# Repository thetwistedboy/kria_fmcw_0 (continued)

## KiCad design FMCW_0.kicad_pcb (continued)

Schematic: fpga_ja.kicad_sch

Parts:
C26: 2.2u; C_0402_1005Metric; Digikey PN 1276-1108-1-ND
C30, C32: 100n; C_0402_1005Metric; Digikey PN 1276-1043-1-ND
D4: GREEN; LED_0603_1608Metric; Digikey PN 160-1446-1-ND
J1: Conn_02x07_Odd_Even; PinHeader_2x07_P2.00mm_Horizontal; Digikey PN WM9841-ND
LCD1: MSP3520; ILI9488_SPI_TFT
R39, R40, R41, R42, R44, R45, R46, R47, R48, R49, R50: 22; R_0402_1005Metric; Digikey PN 541-22.0LCT-ND
R43, R101, R102: 0; R_0402_1005Metric; Digikey PN 311-0.0JRCT-ND
R95: 470; R_0402_1005Metric; Digikey PN 311-470LRCT-ND
R99, R100: 4.7k; R_0402_1005Metric; Digikey PN 311-4.7KJRCT-ND
R103: DNI; R_0402_1005Metric
SW2: SW_Push; SW_Push_1P1T_NO_CK_KMR2; Digikey PN 108-KMR211GLFSCT-ND
SW3: SW_DIP_x04; SW_DIP_SPSTx04_Slide_Omron_A6H-4101_W6.15mm_P1.27mm; Digikey PN 39-A6H-4101-ND
TP1, TP2, TP3: TestPoint; TestPoint_Keystone_5015_Micro_Mini
U16: Kria K24 SoM; Kria_K24
U31: MCP3221; SOT-23-5; Digikey PN MCP3221A5T-E/OTCT-ND

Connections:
+1V8: J1.2, U16.JA_D1 (VCCO_HPA), U16.JA_D2 (VCCO_HPA); also elsewhere on the board
+3V3: C26.1, C30.2, C32.2, LCD1.1 (VCC), R99.2, R100.2, U16.JA_B13 (VCCO_HDA), U16.JA_B14 (VCCO_HDA), U31.1 (V_{DD}); also elsewhere on the board
+5V0: U16.JA_A59 (VCC_SOM), U16.JA_A60 (VCC_SOM), U16.JA_B60 (VCC_SOM), U16.JA_C59 (VCC_SOM), U16.JA_C60 (VCC_SOM), U16.JA_D60 (VCC_SOM); also elsewhere on the board
/RFFE/rf_ps_pg: U16.JA_C15 (PS_POR_B); also elsewhere on the board
/RFFE/rffe_ps_en: R101.2, R103.1; also elsewhere on the board
/RFFE/sample_clk: U16.JA_D16 (HDA_00_CC); also elsewhere on the board
/RFFE/src_ce: U16.JA_A4 (HPA_06N); also elsewhere on the board
/RFFE/src_clk: U16.JA_A6 (HPA_CLK0P_CLK); also elsewhere on the board
/RFFE/src_data: U16.JA_B1 (HPA_05P_CC); also elsewhere on the board
/RFFE/src_le: U16.JA_A3 (HPA_06P); also elsewhere on the board
/RFFE/src_mod: U16.JA_A7 (HPA_CLK0N); also elsewhere on the board
/RFFE/src_muxout: U16.JA_B2 (HPA_05N_CC); also elsewhere on the board
/RFFE/src_trig1: U16.JA_D4 (HPA_02P); also elsewhere on the board
/RFFE/src_trig2: U16.JA_D5 (HPA_02N); also elsewhere on the board
/efuse/Imon: U31.3 (A_{IN}); also elsewhere on the board
/fpga/5V0_PG: U16.JA_B26 (PWROFF_C2M_B); also elsewhere on the board
/fpga/eth/eth_rx_clk: U16.JA_D32 (MIO44); also elsewhere on the board
/fpga/eth/eth_rx_ctrl: U16.JA_C36 (MIO49); also elsewhere on the board
/fpga/eth/eth_rx_d0: U16.JA_D33 (MIO45); also elsewhere on the board
/fpga/eth/eth_rx_d1: U16.JA_D34 (MIO46); also elsewhere on the board
/fpga/eth/eth_rx_d2: U16.JA_C34 (MIO47); also elsewhere on the board
/fpga/eth/eth_rx_d3: U16.JA_C35 (MIO48); also elsewhere on the board
/fpga/eth/eth_tx_clk: U16.JA_B32 (MIO38); also elsewhere on the board
/fpga/eth/eth_tx_ctrl: U16.JA_A36 (MIO43); also elsewhere on the board
/fpga/eth/eth_tx_d0: U16.JA_B33 (MIO39); also elsewhere on the board
/fpga/eth/eth_tx_d1: U16.JA_B34 (MIO40); also elsewhere on the board
/fpga/eth/eth_tx_d2: U16.JA_A34 (MIO41); also elsewhere on the board
/fpga/eth/eth_tx_d3: U16.JA_A35 (MIO42); also elsewhere on the board
/fpga/eth/md_mdc: U16.JA_D13 (HPA_14P); also elsewhere on the board
/fpga/eth/md_mdio: U16.JA_D14 (HPA_14N); also elsewhere on the board
/fpga/fpga_ja/PS_SRST_N: J1.14, SW2.2, U16.JA_C16 (PS_SRST_C2M_B)
/fpga/fpga_ja/PS_SUPPLY_START: R102.2, R103.2
/fpga/fpga_ja/TCK: R41.2, U16.JA_A25 (JTAG_TCK_C2M)
/fpga/fpga_ja/TDI: R39.2, U16.JA_A24 (JTAG_TDI_C2M)
/fpga/fpga_ja/TDO: R40.2, U16.JA_A23 (JTAG_TDO_M2C)
/fpga/fpga_ja/TMS: R42.2, U16.JA_A22 (JTAG_TMS_C2M)
/fpga/fpga_ja/i2c_33_scl: R99.1, U16.JA_C22 (HDA_18), U31.5 (SCL)
/fpga/fpga_ja/i2c_33_sda: R100.1, U16.JA_C23 (HDA_19), U31.4 (SDA)
/fpga/fpga_ja/tft_cs_n: R44.1, U16.JA_D22 (HDA_14)
/fpga/fpga_ja/tft_dc: R46.1, U16.JA_D20 (HDA_12)
/fpga/fpga_ja/tft_led: R49.1, U16.JA_C19 (HDA_07)
/fpga/fpga_ja/tft_miso: R50.1, U16.JA_C18 (HDA_06)
/fpga/fpga_ja/tft_mosi: R47.1, U16.JA_D18 (HDA_02)
/fpga/fpga_ja/tft_rst: R45.1, U16.JA_D21 (HDA_13)
/fpga/fpga_ja/tft_sck: R48.1, U16.JA_D17 (HDA_01)
/fpga/fpga_ja/uart_rxd: U16.JA_A43 (MIO74); also elsewhere on the board
/fpga/fpga_ja/uart_txd: U16.JA_A44 (MIO75); also elsewhere on the board
/fpga/fpga_ja/ulpi_clkout: U16.JA_D36 (MIO52); also elsewhere on the board
/fpga/fpga_ja/ulpi_d0: U16.JA_C39 (MIO56); also elsewhere on the board
/fpga/fpga_ja/ulpi_d1: U16.JA_C40 (MIO57); also elsewhere on the board
/fpga/fpga_ja/ulpi_d2: U16.JA_D38 (MIO54); also elsewhere on the board
/fpga/fpga_ja/ulpi_d3: U16.JA_B41 (MIO59); also elsewhere on the board
/fpga/fpga_ja/ulpi_d4: U16.JA_B42 (MIO60); also elsewhere on the board
/fpga/fpga_ja/ulpi_d5: U16.JA_A38 (MIO61); also elsewhere on the board
/fpga/fpga_ja/ulpi_d6: U16.JA_A39 (MIO62); also elsewhere on the board
/fpga/fpga_ja/ulpi_d7: U16.JA_A40 (MIO63); also elsewhere on the board
/fpga/fpga_ja/ulpi_dir: U16.JA_D37 (MIO53); also elsewhere on the board
/fpga/fpga_ja/ulpi_nxt: U16.JA_C38 (MIO55); also elsewhere on the board
/fpga/fpga_ja/ulpi_stp: U16.JA_B40 (MIO58); also elsewhere on the board
/fpga/fpga_ja/usb_reset: U16.JA_D40 (MIO64); also elsewhere on the board
GND: C26.2, C30.1, C32.1, D4.1 (K), J1.1, J1.3, J1.5, J1.7, J1.9, J1.11, J1.13, LCD1.2 (GND), R43.1, SW2.1, SW3.5, SW3.6, SW3.7, SW3.8, U16.JA_A2 (GND), U16.JA_A5 (GND), U16.JA_A8 (GND), U16.JA_A11 (GND), U16.JA_A14 (GND), U16.JA_A18 (GND), U16.JA_A21 (GND), U16.JA_A26 (GND), U16.JA_A33 (GND), U16.JA_A37 (GND), U16.JA_A41 (GND), U16.JA_A45 (GND), U16.JA_A46 (GND), U16.JA_A49 (GND), U16.JA_A50 (GND), U16.JA_A53 (GND), U16.JA_A54 (GND), U16.JA_A57 (GND), U16.JA_A58 (GND), U16.JA_B3 (GND), U16.JA_B6 (GND), U16.JA_B9 (GND), U16.JA_B12 (GND), U16.JA_B15 (GND), U16.JA_B19 (GND), U16.JA_B23 (GND), U16.JA_B27 (GND), U16.JA_B31 (GND), U16.JA_B35 (GND), U16.JA_B39 (GND), U16.JA_B43 (GND), U16.JA_B47 (GND), U16.JA_B48 (GND), U16.JA_B51 (GND), U16.JA_B52 (GND), U16.JA_B55 (GND), U16.JA_B56 (GND), U16.JA_B59 (GND), U16.JA_C1 (GND), U16.JA_C2 (GND), U16.JA_C5 (GND), U16.JA_C8 (GND), U16.JA_C11 (GND), U16.JA_C14 (GND), U16.JA_C17 (GND), U16.JA_C21 (GND), U16.JA_C25 (GND), U16.JA_C29 (GND), U16.JA_C33 (GND), U16.JA_C37 (GND), U16.JA_C41 (GND), U16.JA_C46 (GND), U16.JA_C49 (GND), U16.JA_C50 (GND), U16.JA_C53 (GND), U16.JA_C54 (GND), U16.JA_C57 (GND), U16.JA_C58 (GND), U16.JA_D3 (GND), U16.JA_D6 (GND), U16.JA_D9 (GND), U16.JA_D12 (GND), U16.JA_D15 (GND), U16.JA_D19 (GND), U16.JA_D23 (GND), U16.JA_D27 (GND), U16.JA_D31 (GND), U16.JA_D35 (GND), U16.JA_D39 (GND), U16.JA_D43 (GND), U16.JA_D47 (GND), U16.JA_D48 (GND), U16.JA_D51 (GND), U16.JA_D52 (GND), U16.JA_D55 (GND), U16.JA_D56 (GND), U16.JA_D59 (GND), U31.2 (V_{SS}); also elsewhere on the board
unnamed: D4.2 (A), R95.1
unnamed: J1.4, R42.1
unnamed: J1.6, R41.1
unnamed: J1.8, R40.1
unnamed: J1.10, R39.1
unnamed: LCD1.3 (CS), R44.2
unnamed: LCD1.5 (DC), R46.2
unnamed: LCD1.8 (LED), R49.2
unnamed: LCD1.4 (RST), R45.2
unnamed: LCD1.7 (SCK), R48.2
unnamed: LCD1.6 (SDI), R47.2
unnamed: LCD1.9 (SDO), R50.2
unnamed: R95.2, U16.JA_B16 (HDA_03)
unnamed: TP3.1 (1_1), U16.JA_A15 (HDA_09)
unnamed: TP1.1 (1_1), U16.JA_A16 (HDA_10)
unnamed: TP2.1 (1_1), U16.JA_A17 (HDA_11)
unnamed: SW3.1, U16.JA_A27 (MODE0_C2M)
unnamed: SW3.2, U16.JA_A28 (MODE1_C2M)
unnamed: SW3.3, U16.JA_A29 (MODE2_C2M)
unnamed: SW3.4, U16.JA_A30 (MODE3_C2M)
unnamed: R101.1, U16.JA_A20 (VCCOEN_PL_M2C)
unnamed: R102.1, U16.JA_A19 (VCCOEN_PS_M2C)
unnamed: R43.2, U16.JA_A1 (VCC_BATT)

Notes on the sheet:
HPIO
MDIO MIO50-51
USB0 MIO52-63
GEM1 MIO38-49

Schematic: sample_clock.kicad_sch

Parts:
C1, C2: 100n; C_0402_1005Metric; Digikey PN 1276-1043-1-ND
FB1: FerriteBead_Small; R_0402_1005Metric; Digikey PN 490-5203-1-ND
R1, R3, R4: 10k; R_0402_1005Metric; Digikey PN RMCF0402FT10K0CT-ND
R2, R6, R7: 22; R_0402_1005Metric; Digikey PN 541-22.0LCT-ND
R5, R8: 49.9; R_0402_1005Metric; Digikey PN P49.9LCT-ND
U3: LMK1C1103A; TSSOP-8_4.4x3mm_P0.65mm; Digikey PN 296-LMK1C1103APWRCT-ND
Y1: ECS-2520MV-160-BN; Oscillator_SMD_ECS_2520MV-xxx-xx-4Pin_2.5x2.0mm; Digikey PN 50-ECS-2520MV-160-BN-TRCT-ND

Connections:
+3V3: C2.1, FB1.1, R4.1, U3.6 (VDD); also elsewhere on the board
/RFFE/ADC/sample_clk: R8.2; also elsewhere on the board
/RFFE/sample_clk: R6.2; also elsewhere on the board
/RFFE/sample_clk_out: R7.2; also elsewhere on the board
/RFFE/sample_clock/clk0: R5.2; also elsewhere on the board
GND: C1.2, C2.2, R3.2, U3.4 (GND), Y1.2 (GND); also elsewhere on the board
unnamed: R4.2, U3.2 (1G)
unnamed: R2.2, R3.1, U3.1 (CLKIN)
unnamed: R5.1, U3.3 (Y0)
unnamed: R6.1, U3.8 (Y1)
unnamed: R7.1, U3.5 (Y2)
unnamed: R8.1, U3.7 (Y3)
unnamed: R2.1, Y1.3 (OUT)
unnamed: R1.1, Y1.1 (Tri-State)
unnamed: C1.1, FB1.2, R1.2, Y1.4 (VDD)

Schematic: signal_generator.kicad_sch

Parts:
C18, C19, C22, C23, C25, C28, C31, C34: 100n; C_0402_1005Metric; Digikey PN 1276-1043-1-ND
C20: 1u; C_0402_1005Metric; Digikey PN 1276-1067-1-ND
C21: 10n; C_0402_1005Metric; Digikey PN 490-1313-2-ND
C24, C27: C_Small; C_0402_1005Metric
C29, C33: 220p; C_0402_1005Metric; Digikey PN 490-1293-1-ND
R16, R17, R20: 49.9; R_0402_1005Metric; Digikey PN P49.9LCT-ND
R18, R19: 10k; R_0402_1005Metric; Digikey PN RMCF0402FT10K0CT-ND
R21: R_Small; R_0402_1005Metric
R22, R23: 18; R_0402_1005Metric; Digikey PN CR0402-FX-18R0GLFCT-ND
R24: 68; R_0402_1005Metric; Digikey PN P68.0LCT-ND
R25: 43; R_0402_1005Metric; Digikey PN 311-43JRCT-ND
R26, R27, R28: 22; R_0402_1005Metric; Digikey PN 541-22.0LCT-ND
RN3, RN4: 22; R_Array_Convex_4x0402; Digikey PN Y7220CT-ND
U10: LMX2491; QFN-24-1EP_4x4mm_P0.5mm_EP2.6x2.6mm; Digikey PN 296-45052-1-ND
U11: MAX275X; MSOP-8_3x3mm_P0.65mm; Digikey PN MAX2750EUA+TCT-ND

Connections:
+3.3VA: C20.1, C21.1, C22.1, C25.1, C29.1, C33.1, R18.1, U10.6 (Vcc), U10.7 (Vcc), U10.8 (Vcc), U10.18 (Vcc), U10.19 (Vcc), U10.22 (Vcp), U11.4 (~SHDN), U11.5 (VCC1), U11.6 (VCC2); also elsewhere on the board
/RFFE/demodulator/LO: R28.2; also elsewhere on the board
/RFFE/sample_clock/clk0: R16.1; also elsewhere on the board
/RFFE/signal_generator/f_out1: R27.2; also elsewhere on the board
/RFFE/src_ce: RN3.7 (R2.2); also elsewhere on the board
/RFFE/src_clk: RN3.6 (R3.2); also elsewhere on the board
/RFFE/src_data: RN4.5 (R4.2); also elsewhere on the board
/RFFE/src_le: RN3.8 (R1.2); also elsewhere on the board
/RFFE/src_mod: RN3.5 (R4.2); also elsewhere on the board
/RFFE/src_muxout: RN4.6 (R3.2); also elsewhere on the board
/RFFE/src_trig1: RN4.7 (R2.2); also elsewhere on the board
/RFFE/src_trig2: RN4.8 (R1.2); also elsewhere on the board
GND: C20.2, C21.2, C22.2, C24.2, C25.2, C29.2, C31.2, C33.2, C34.2, R17.1, R19.2, R20.2, R21.2, R24.2, U10.1 (GND), U10.2 (GND), U10.3 (GND), U10.11 (GND), U10.25 (EP), U11.3 (GND), U11.8 (GND); also elsewhere on the board
unnamed: C18.1, R16.2
unnamed: C19.1, R17.2
unnamed: C23.2, R20.1
unnamed: C27.2, R21.1
unnamed: C28.2, R23.1
unnamed: R23.2, R24.1, R25.1
unnamed: R25.2, R26.2, R27.1, R28.1
unnamed: RN3.1 (R1.1), U10.15 (DATA)
unnamed: RN3.2 (R2.1), U10.14 (CLK)
unnamed: R19.1, RN3.3 (R3.1), U10.13 (CE)
unnamed: RN3.4 (R4.1), U10.12 (MOD)
unnamed: RN4.1 (R1.1), U10.21 (TRIG2)
unnamed: RN4.2 (R2.1), U10.20 (TRIG1)
unnamed: RN4.3 (R3.1), U10.17 (MUXOUT)
unnamed: R18.2, RN4.4 (R4.1), U10.16 (LE)
unnamed: C24.1, C27.1, R22.1, U10.24 (CPout)
unnamed: C28.1, U10.5 (Fin_n)
unnamed: C23.1, U10.4 (Fin_p)
unnamed: C19.2, U10.10 (OSCin_n)
unnamed: C18.2, U10.9 (OSCin_p)
unnamed: C34.1, U11.1 (BYP)
unnamed: R26.1, U11.7 (OUT)
unnamed: C31.1, R22.2, U11.2 (TUNE)

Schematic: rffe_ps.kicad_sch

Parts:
C3, C4, C7, C8: 1u; C_0402_1005Metric; Digikey PN 1276-1067-1-ND
C5, C6: 22u; C_0805_2012Metric; Digikey PN 1276-6786-1-ND
C9, C10: 2.2u; C_0402_1005Metric; Digikey PN 1276-1108-1-ND
C11, C12: 100n; C_0402_1005Metric; Digikey PN 1276-1043-1-ND
FB2, FB3: FerriteBead_Small; R_0402_1005Metric; Digikey PN 490-5203-1-ND
L1: 4.7u; L_Wuerth_MAPI-4020; Digikey PN 732-11316-1-ND
R9, R12: 10k; R_0402_1005Metric; Digikey PN RMCF0402FT10K0CT-ND
R10: 22; R_0402_1005Metric; Digikey PN 541-22.0LCT-ND
R11: 59k; R_0402_1005Metric; Digikey PN 311-59KLRCT-ND
U4: AP63200WU; TSOT-23-6; Digikey PN 31-AP63201QWU-7CT-ND
U5: TLV76750QWDRBxQ1; VSON-8-1EP_3x3mm_P0.65mm_EP1.65x2.4mm; Digikey PN 296-TLV76750QWDRBRQ1CT-ND
U6: TLV76733QWDRBxQ1; VSON-8-1EP_3x3mm_P0.65mm_EP1.65x2.4mm; Digikey PN 296-TLV76733QWDRBRQ1CT-ND
U7: TPS3839K50DBZR; SOT-23; Digikey PN 296-35472-1-ND
U8: TPS3839K33DBZR; SOT-23; Digikey PN 296-35471-1-ND

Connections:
+3.3VA: FB3.2; also elsewhere on the board
+5VA: FB2.2; also elsewhere on the board
/RFFE/Vin: C3.1, U4.3 (IN); also elsewhere on the board
/RFFE/rf_ps_pg: U7.2 (~RESET), U8.2 (~RESET); also elsewhere on the board
/RFFE/rffe_ps_en: R9.2, R10.1; also elsewhere on the board
GND: C3.2, C5.1, C6.1, C7.2, C8.2, C9.2, C10.2, C11.1, C12.1, R9.1, R12.1, U4.4 (GND), U5.4 (GND), U5.6 (GND), U5.9 (PAD), U6.4 (GND), U6.6 (GND), U6.9 (PAD), U7.1 (GND), U8.1 (GND); also elsewhere on the board
unnamed: C4.1, U4.6 (BST)
unnamed: R10.2, U4.2 (EN)
unnamed: R11.2, R12.2, U4.1 (FB)
unnamed: C4.2, L1.1, U4.5 (SW)
unnamed: C5.2, C6.2, C7.1, C8.1, L1.2, R11.1, U5.5 (EN), U5.8 (IN), U6.5 (EN), U6.8 (IN)
unnamed: C10.1, C11.2, FB2.1, U5.1 (OUT), U5.3 (SNS), U7.3 (VDD)
unnamed: C9.1, C12.2, FB3.1, U6.1 (OUT), U6.3 (SNS), U8.3 (VDD)

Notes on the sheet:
BAD REPLACE WITH OPEN DRAIN PART

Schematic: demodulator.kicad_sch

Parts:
C35, C36, C37: 100n; C_0402_1005Metric; Digikey PN 1276-1043-1-ND
C38, C39, C40, C41, C42, C43, C44: 100p; C_0402_1005Metric; Digikey PN 1292-1637-1-ND
C45, C46, C47, C48: 10u; C_0603_1608Metric; Digikey PN 490-7202-1-ND
C49, C50: 82p; C_0402_1005Metric; Digikey PN 490-7310-1-ND
C51, C52: 360p; C_0402_1005Metric; Digikey PN 399-14907-1-ND
C53, C54: 430p; C_0402_1005Metric; Digikey PN 490-GCM1555C1H431JA16DCT-ND
L2, L3, L4, L5: 310n; L_0402_1005Metric; Digikey PN 445-6324-1-ND
L6, L7, L8, L9: 550n; L_0402_1005Metric; Digikey PN 587-6432-1-ND
R29, R30: DNI; R_0402_1005Metric
R31: 10k; R_0402_1005Metric; Digikey PN RMCF0402FT10K0CT-ND
R32: 1.5k; R_0402_1005Metric; Digikey PN P1.50KLCT-ND
R33, R34: 499; R_0402_1005Metric; Digikey PN P499LCT-ND
U12, U13: 5400BL15B050; Balun_Johanson_5400BL15B050E; Digikey PN 712-2450FB15A0050001ECT-ND
U14: ADL5380; LFCSP-24-1EP_4x4mm_P0.5mm_EP2.3x2.3mm; Digikey PN 505-ADL5380ACPZ-R7CT-ND

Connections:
+5VA: C35.2, C36.2, C37.2, C40.2, C41.2, C42.2, R32.1, U14.6 (VCC1), U14.13 (VCC2), U14.24 (VCC3); also elsewhere on the board
/RFFE/ADC/ADCI_N: C53.1, L6.2, R33.1; also elsewhere on the board
/RFFE/ADC/ADCI_P: C53.2, L7.2, R33.2; also elsewhere on the board
/RFFE/ADC/ADCQ_N: C54.2, L9.2, R34.2; also elsewhere on the board
/RFFE/ADC/ADCQ_P: C54.1, L8.2, R34.1; also elsewhere on the board
/RFFE/demodulator/LO: U12.1; also elsewhere on the board
/RFFE/demodulator/RF_in: U13.1; also elsewhere on the board
GND: C35.1, C36.1, C37.1, C40.1, C41.1, C42.1, R29.2, R30.2, R31.2, U12.2 (GND), U12.5 (GND), U13.2 (GND), U13.5 (GND), U14.1 (GND), U14.2 (GND), U14.5 (GND), U14.8 (GND), U14.11 (GND), U14.14 (GND), U14.17 (GND), U14.18 (GND), U14.20 (GND), U14.23 (GND), U14.25 (EP); also elsewhere on the board
unnamed: C38.1, U12.3
unnamed: C39.1, U12.4
unnamed: C43.1, R29.1, U13.3
unnamed: C44.1, R30.1, U13.4
unnamed: C45.2, C49.1, L2.1
unnamed: C46.2, C49.2, L3.1
unnamed: C47.2, C50.1, L4.1
unnamed: C48.2, C50.2, L5.1
unnamed: C51.1, L2.2, L6.1
unnamed: C51.2, L3.2, L7.1
unnamed: C52.1, L4.2, L8.1
unnamed: C52.2, L5.2, L9.1
unnamed: R32.2, U14.19 (ADJ)
unnamed: R31.1, U14.7 (ENBL)
unnamed: C46.1, U14.3 (IHI)
unnamed: C45.1, U14.4 (ILO)
unnamed: C38.2, U14.10 (LOIN)
unnamed: C39.2, U14.9 (LOIP)
unnamed: C47.1, U14.16 (QHI)
unnamed: C48.1, U14.15 (QLO)
unnamed: C44.2, U14.21 (RFIN)
unnamed: C43.2, U14.22 (RFIP)

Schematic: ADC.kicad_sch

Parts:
C13, C15: 100n; C_0402_1005Metric; Digikey PN 1276-1043-1-ND
C14: 100p; C_0402_1005Metric; Digikey PN 1292-1637-1-ND
C16: 10n; C_0402_1005Metric; Digikey PN 490-1313-2-ND
C17: 1u; C_0402_1005Metric; Digikey PN 1276-1067-1-ND
FB4: FerriteBead_Small; R_0402_1005Metric; Digikey PN 490-5203-1-ND
R13, R14: 10k; R_0402_1005Metric; Digikey PN RMCF0402FT10K0CT-ND
R15: 22; R_0402_1005Metric; Digikey PN 541-22.0LCT-ND
RN1, RN2: 22; R_Array_Convex_4x0402; Digikey PN Y7220CT-ND
U9: MCP3911; UQFN-20-1EP_4x4mm_P0.5mm_EP2.8x2.8mm; Digikey PN MCP3911A0T-E/MLCT-ND

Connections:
+3.3VA: FB4.1, R15.2; also elsewhere on the board
/RFFE/ADC/ADCI_N: U9.3 (CH1-); also elsewhere on the board
/RFFE/ADC/ADCI_P: U9.4 (CH1+); also elsewhere on the board
/RFFE/ADC/ADCQ_N: U9.2 (CH0-); also elsewhere on the board
/RFFE/ADC/ADCQ_P: U9.1 (CH0+); also elsewhere on the board
/RFFE/ADC/adc_dvdd: C13.1, FB4.2, R13.2, U9.19 (DVDD)
/RFFE/ADC/sample_clk: U9.12 (OSC1/CLKI); also elsewhere on the board
/RFFE/adc_cs_n: RN2.8 (R1.2); also elsewhere on the board
/RFFE/adc_dr_n: RN2.7 (R2.2); also elsewhere on the board
/RFFE/adc_mdat0: RN2.6 (R3.2); also elsewhere on the board
/RFFE/adc_mdat1: RN2.5 (R4.2); also elsewhere on the board
/RFFE/adc_reset_n: RN1.8 (R1.2); also elsewhere on the board
/RFFE/adc_sck: RN1.5 (R4.2); also elsewhere on the board
/RFFE/adc_sdi: RN1.7 (R2.2); also elsewhere on the board
/RFFE/adc_sdo: RN1.6 (R3.2); also elsewhere on the board
GND: C13.2, C14.2, C15.2, C16.2, C17.2, R14.1, U9.5 (AGND), U9.7 (REFIN-), U9.8 (DGND), U9.21 (EP); also elsewhere on the board
unnamed: R14.2, RN1.1 (R1.1), U9.18 (~RESET)
unnamed: RN1.2 (R2.1), U9.17 (SDI)
unnamed: RN1.3 (R3.1), U9.16 (SDO)
unnamed: RN1.4 (R4.1), U9.15 (SCK)
unnamed: R13.1, RN2.1 (R1.1), U9.14 (~CS)
unnamed: RN2.2 (R2.1), U9.11 (~DR)
unnamed: RN2.3 (R3.1), U9.10 (MDAT0)
unnamed: RN2.4 (R4.1), U9.9 (MDAT1)
unnamed: C14.1, C16.1, C17.1, R15.1, U9.20 (AVDD)
unnamed: C15.1, U9.6 (REFIN+/OUT)

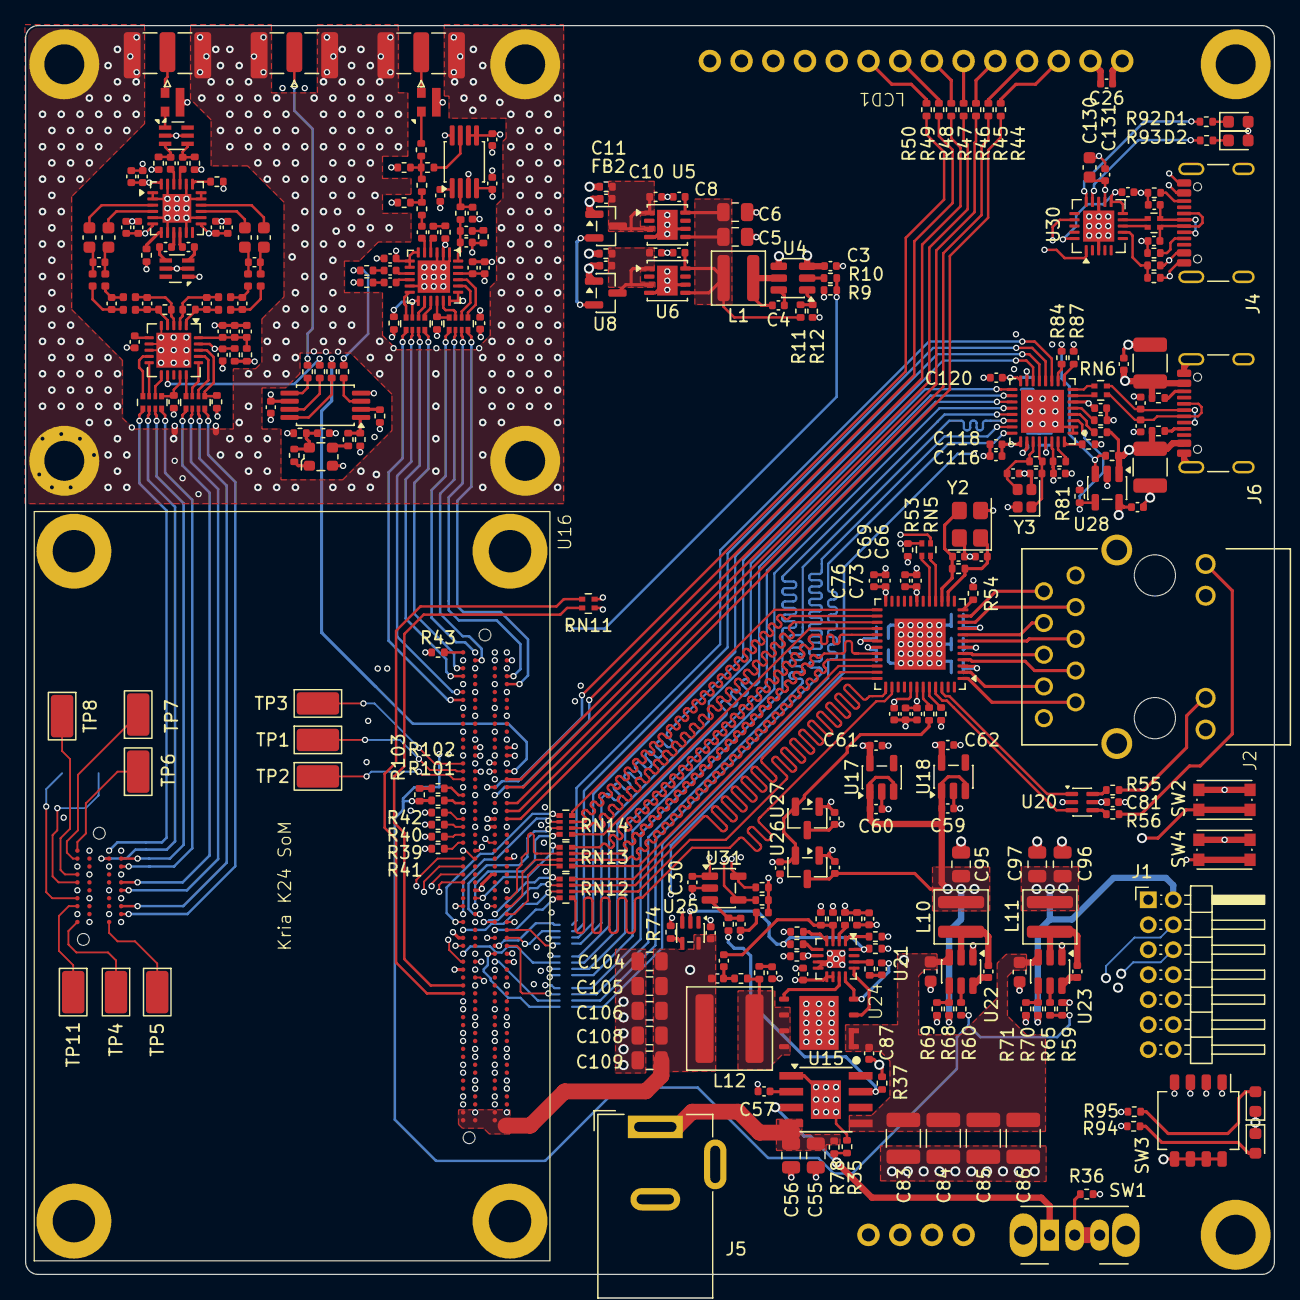
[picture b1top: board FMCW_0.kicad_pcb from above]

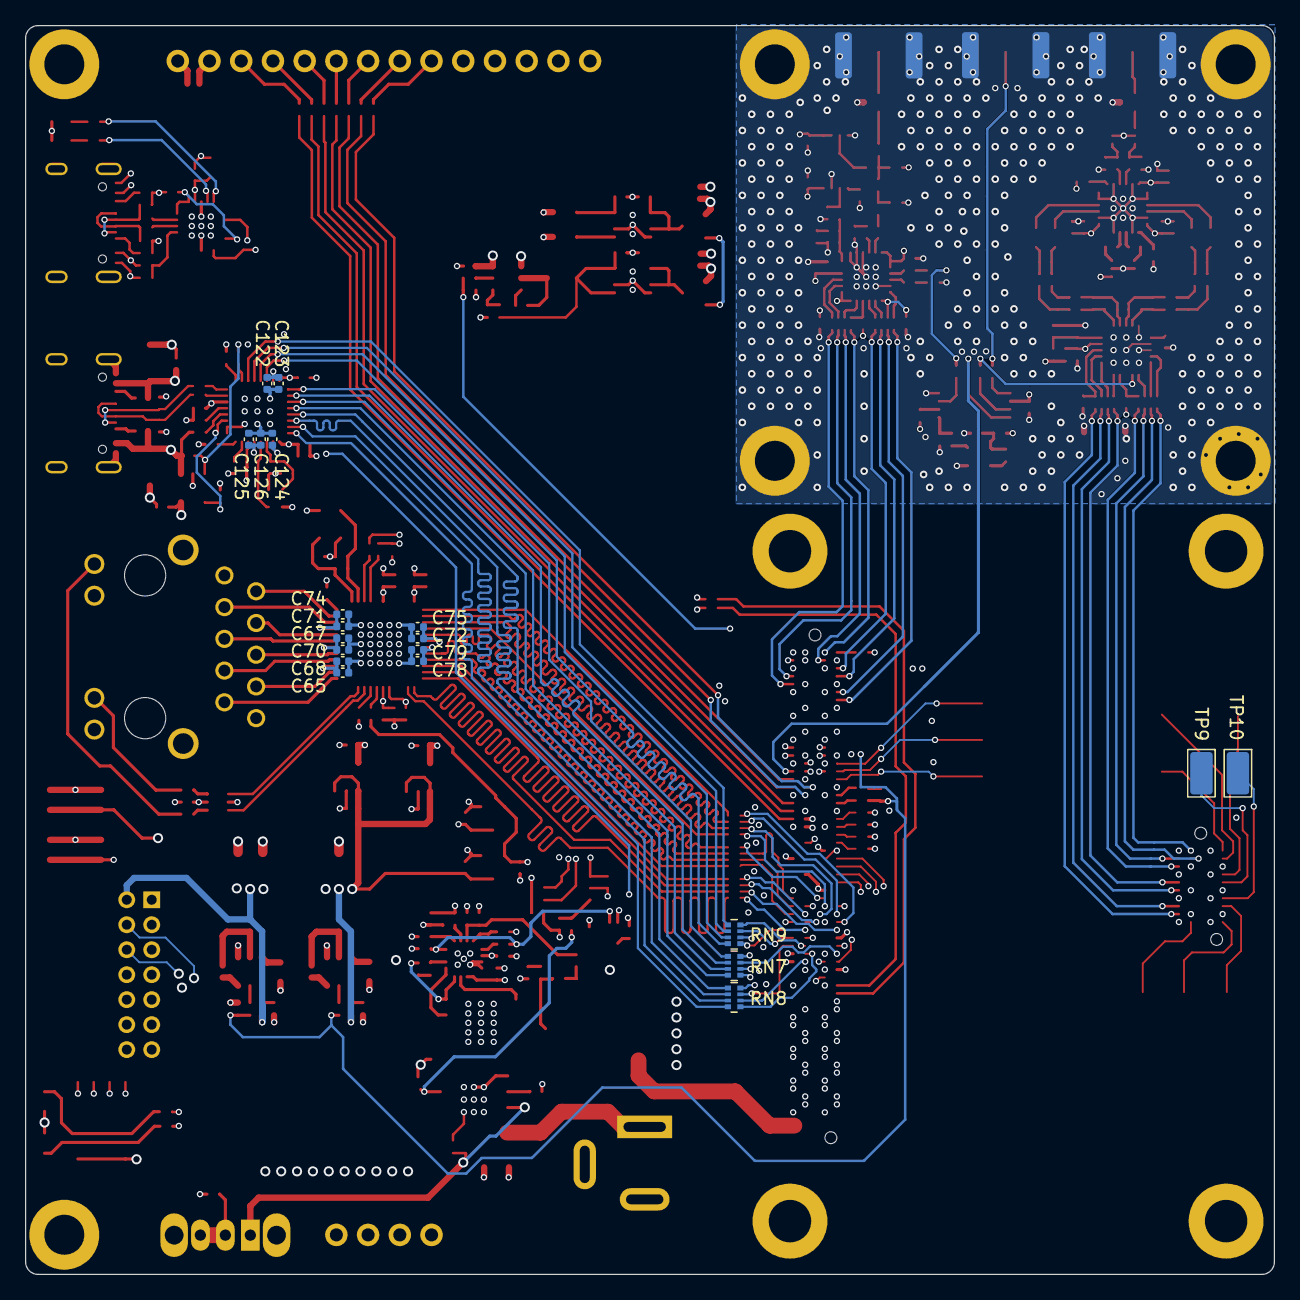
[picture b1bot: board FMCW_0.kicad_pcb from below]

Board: 6 copper layers, 100.0 x 100.0 mm, 332 parts (20 on the bottom side), 299 nets.

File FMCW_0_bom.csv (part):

Reference,Qty,Value,DNP,Exclude from BOM,Exclude from Board,Footprint,Digikey PN
"C1,C2,C11,C12,C13,C15,C18,C19,C22,C23,C25,C28,C30,C31,C32,C34,C35,C36,C37,C65,C66,C67,C71,C72,C73,C77,C78,C80,C81,C91,C92,C93,C94,C99,C100,C101,C107,C113,C118,C119,C120,C121,C123,C124,C125,C129,C131",60,100n,,,,Capacitor_SMD:C_0402_1005Metric,1276-1043-1-ND
"C3,C4,C7,C8,C17,C20,C59,C60,C61,C62,C68,C69,C70,C74,C75,C76,C79,C82,C87,C117",25,1u,,,,Capacitor_SMD:C_0402_1005Metric,1276-1067-1-ND
"C5,C6",5,22u,,,,Capacitor_SMD:C_0805_2012Metric,1276-6786-1-ND
"C55,C56",5,22u,,,,Capacitor_SMD:C_0805_2012Metric,587-5466-1-ND
"C104,C105,C106,C108,C109",10,22u,,,,Capacitor_SMD:C_0805_2012Metric,587-6359-1-ND
"C9,C10,C26",10,2.2u,,,,Capacitor_SMD:C_0402_1005Metric,1276-1108-1-ND
"C14,C38,C39,C40,C41,C42,C43,C44",10,100p,,,,Capacitor_SMD:C_0402_1005Metric,1292-1637-1-ND
"C16,C21",10,10n,,,,Capacitor_SMD:C_0402_1005Metric,490-1313-2-ND
"C29,C33",10,220p,,,,Capacitor_SMD:C_0402_1005Metric,490-1293-1-ND
"C45,C46,C47,C48,C89,C90",10,10u,,,,Capacitor_SMD:C_0603_1608Metric,490-7202-1-ND
"C49,C50",10,82p,,,,Capacitor_SMD:C_0402_1005Metric,490-7310-1-ND
"C51,C52",10,360p,,,,Capacitor_SMD:C_0402_1005Metric,399-14907-1-ND
"C53,C54",10,430p,,,,Capacitor_SMD:C_0402_1005Metric,490-GCM1555C1H431JA16DCT-ND
C57,10,3.3n,,,,Capacitor_SMD:C_0402_1005Metric,1276-1552-1-ND
"C58,C103",10,33n,,,,Capacitor_SMD:C_0402_1005Metric,587-3466-1-ND
"C63,C64",10,27p,,,,Capacitor_SMD:C_0402_1005Metric,490-5869-1-ND
"C83,C84,C85,C86",10,22u,,,,Capacitor_SMD:C_1210_3225Metric,587-5951-1-ND
"C88,C102",10,1n,,,,Capacitor_SMD:C_0402_1005Metric,490-3244-1-ND
"C95,C96,C97",5,47u,,,,Capacitor_SMD:C_0805_2012Metric,490-13249-1-ND
C98,10,4.7n,,,,Capacitor_SMD:C_0402_1005Metric,490-1308-1-ND
"C110,C112,C127,C128",10,47p,,,,Capacitor_SMD:C_0402_1005Metric,490-5942-1-ND
"C111,C132",3,100u,,,,Capacitor_SMD:C_1210_3225Metric,490-10534-1-ND
"C114,C115",10,8p,,,,Capacitor_SMD:C_0402_1005Metric,1276-CL05C080DB51PNCCT-ND
"C116,C122,C126",5,4.7u,,,,Capacitor_SMD:C_0402_1005Metric,490-14306-1-ND
C130,2,4.7u,,,,Capacitor_SMD:C_0603_1608Metric,1276-2087-1-ND
"D1,D2",2,YELLOW,,,,LED_SMD:LED_0603_1608Metric,160-1437-1-ND
D3,1,RED,,,,LED_SMD:LED_0603_1608Metric,160-1436-1-ND
D4,1,GREEN,,,,LED_SMD:LED_0603_1608Metric,160-1446-1-ND
"FB1,FB2,FB3,FB4",10,FerriteBead_Small,,,,Resistor_SMD:R_0402_1005Metric,490-5203-1-ND
J1,1,Conn_02x07_Odd_Even,,,,Connector_PinHeader_2.00mm:PinHeader_2x07_P2.00mm_Horizontal,WM9841-ND
J2,1,HFJ11-1G41E-L12RL,,,,fmcw_:HFJ11-1G41E-L12RL,5843-HFJ11-1G41E-L12RL-ND
"J4,J6",2,USB_C_Receptacle_USB2.0_16P,,,,Connector_USB:USB_C_Receptacle_GCT_USB4105-xx-A_16P_TopMnt_Horizontal,2073-USB4215-03-ACT-ND
J5,1,Barrel_Jack_Switch,,,,Connector_BarrelJack:BarrelJack_Wuerth_6941xx301002,732-5934-ND
"L1,L11",2,4.7u,,,,Inductor_SMD:L_Wuerth_MAPI-4020,732-11316-1-ND
"L2,L3,L4,L5",5,310n,,,,Inductor_SMD:L_0402_1005Metric,445-6324-1-ND
"L6,L7,L8,L9",5,550n,,,,Inductor_SMD:L_0402_1005Metric,587-6432-1-ND
L10,1,10u,,,,Inductor_SMD:L_Wuerth_MAPI-4030,732-11206-1-ND
L12,1,4.7u,,,,Inductor_SMD:L_Wuerth_XHMI-6060,732-744393445047CT-ND
"R1,R3,R4,R9,R12,R13,R14,R18,R19,R31,R35,R59,R76,R91",20,10k,,,,Resistor_SMD:R_0402_1005Metric,RMCF0402FT10K0CT-ND
"R2,R6,R7,R10,R15,R26,R27,R28,R39,R40,R41,R42,R44,R45,R46,R47,R48,R49,R50,R60,R65,R74",30,22,,,,Resistor_SMD:R_0402_1005Metric,541-22.0LCT-ND
"R5,R8,R16,R17,R20",10,49.9,,,,Resistor_SMD:R_0402_1005Metric,P49.9LCT-ND
R11,10,59k,,,,Resistor_SMD:R_0402_1005Metric,311-59KLRCT-ND
"R22,R23",10,18,,,,Resistor_SMD:R_0402_1005Metric,CR0402-FX-18R0GLFCT-ND
R24,10,68,,,,Resistor_SMD:R_0402_1005Metric,P68.0LCT-ND
R25,10,43,,,,Resistor_SMD:R_0402_1005Metric,311-43JRCT-ND
"R32,R53",10,1.5k,,,,Resistor_SMD:R_0402_1005Metric,P1.50KLCT-ND
"R33,R34",10,499,,,,Resistor_SMD:R_0402_1005Metric,P499LCT-ND
"R36,R55,R56",10,220,,,,Resistor_SMD:R_0402_1005Metric,311-220LRCT-ND
R37,10,909,,,,Resistor_SMD:R_0402_1005Metric,YAG3256CT-ND
"R38,R64,R79",10,1k,,,,Resistor_SMD:R_0402_1005Metric,311-1.00KLRCT-ND
"R43,R51,R83,R84,R85,R87,R101,R102",10,0,,,,Resistor_SMD:R_0402_1005Metric,311-0.0JRCT-ND
R52,10,2.2k,,,,Resistor_SMD:R_0402_1005Metric,RMCF0402FT2K20CT-ND
R54,10,11k,,,,Resistor_SMD:R_0402_1005Metric,P11KDCCT-ND
R57,10,866k,,,,Resistor_SMD:R_0402_1005Metric,RMCF0402FT866KCT-ND
R58,10,39k,,,,Resistor_SMD:R_0402_1005Metric,311-39.0KLRCT-ND
R61,10,200k,,,,Resistor_SMD:R_0402_1005Metric,311-200KLRCT-ND
"R62,R67,R68,R70",10,100k,,,,Resistor_SMD:R_0402_1005Metric,311-100KLRCT-ND
R63,10,26.1k,,,,Resistor_SMD:R_0402_1005Metric,311-26.1KLRCT-ND
R66,10,5.23,,,,Resistor_SMD:R_0402_1005Metric,541-5.23LLCT-ND
"R69,R78",10,22k,,,,Resistor_SMD:R_0402_1005Metric,RMCF0402FT10K0CT-ND
R71,10,49.9k,,,,Resistor_SMD:R_0402_1005Metric,P49.9KLCT-ND
R72,10,1,,,,Resistor_SMD:R_0402_1005Metric,541-1.00LLCT-ND
R73,10,10,,,,Resistor_SMD:R_0402_1005Metric,311-10.0LRCT-ND
R75,10,71.5k,,,,Resistor_SMD:R_0402_1005Metric,RMCF0402FT71K5CT-ND
"R77,R98",10,1M,,,,Resistor_SMD:R_0402_1005Metric,311-1.00MLRCT-ND
R80,10,820,,,,Resistor_SMD:R_0402_1005Metric,311-820LRCT-ND
R81,10,20k,,,,Resistor_SMD:R_0402_1005Metric,311-20.0KLRCT-ND
R82,10,12k,,,,Resistor_SMD:R_0402_1005Metric,311-12.0KLRCT-ND
"R88,R89",10,5.1k,,,,Resistor_SMD:R_0402_1005Metric,P5.10KLCT-ND
"R90,R99,R100",10,4.7k,,,,Resistor_SMD:R_0402_1005Metric,311-4.7KJRCT-ND
"R92,R93,R94,R95",10,470,,,,Resistor_SMD:R_0402_1005Metric,311-470LRCT-ND
"R96,R97",10,56k,,,,Resistor_SMD:R_0402_1005Metric,311-20.0KLRCT-ND
"RN1,RN2,RN3,RN4,RN7,RN8,RN9,RN12,RN13,RN14",20,22,,,,Resistor_SMD:R_Array_Convex_4x0402,Y7220CT-ND
"RN5,RN6,RN10,RN11",10,27,,,,Resistor_SMD:R_Array_Convex_2x0402,Y5270CT-ND
SW1,1,SW_SPDT,,,,Button_Switch_THT:SW_Slide_SPDT_Angled_CK_OS102011MA1Q,CKN9559-ND
"SW2,SW4",2,SW_Push,,,,Button_Switch_SMD:SW_Push_1P1T_NO_CK_KMR2,108-KMR211GLFSCT-ND
SW3,1,SW_DIP_x04,,,,Button_Switch_SMD:SW_DIP_SPSTx04_Slide_Omron_A6H-4101_W6.15mm_P1.27mm,39-A6H-4101-ND
"U1,U2",5,PAT1220-C-6DB,,,,RF_Converter:RF_Attenuator_Susumu_PAT1220,PAT126CT-ND
U3,1,LMK1C1103A,,,,Package_SO:TSSOP-8_4.4x3mm_P0.65mm,296-LMK1C1103APWRCT-ND
U4,1,AP63200WU,,,,Package_TO_SOT_SMD:TSOT-23-6,31-AP63201QWU-7CT-ND
U5,1,TLV76750QWDRBxQ1,,,,Package_SON:VSON-8-1EP_3x3mm_P0.65mm_EP1.65x2.4mm,296-TLV76750QWDRBRQ1CT-ND
U6,1,TLV76733QWDRBxQ1,,,,Package_SON:VSON-8-1EP_3x3mm_P0.65mm_EP1.65x2.4mm,296-TLV76733QWDRBRQ1CT-ND
U7,1,TPS3839K50DBZR,,,,Package_TO_SOT_SMD:SOT-23,296-35472-1-ND
"U8,U26",2,TPS3839K33DBZR,,,,Package_TO_SOT_SMD:SOT-23,296-35471-1-ND
U9,1,MCP3911,,,,Package_DFN_QFN:UQFN-20-1EP_4x4mm_P0.5mm_EP2.8x2.8mm,MCP3911A0T-E/MLCT-ND
U10,1,LMX2491,,,,Package_DFN_QFN:QFN-24-1EP_4x4mm_P0.5mm_EP2.6x2.6mm,296-45052-1-ND
U11,1,MAX275X,,,,Package_SO:MSOP-8_3x3mm_P0.65mm,MAX2750EUA+TCT-ND
"U12,U13",2,5400BL15B050,,,,RF_Converter:Balun_Johanson_5400BL15B050E,712-2450FB15A0050001ECT-ND
U14,1,ADL5380,,,,Package_CSP:LFCSP-24-1EP_4x4mm_P0.5mm_EP2.3x2.3mm,505-ADL5380ACPZ-R7CT-ND
U15,1,TPS259620,,,,Package_SO:TI_SO-PowerPAD-8,296-TPS259620DDARCT-ND
U17,1,AP2127K-1.0,,,,Package_TO_SOT_SMD:SOT-23-5,31-AP2127K-1.0TRG1CT-ND
U18,1,AP2127K-2.5,,,,Package_TO_SOT_SMD:SOT-23-5,31-AP2127K-2.5TRG1CT-ND
U19,1,DP83867CRRGZR,,,,Package_DFN_QFN:VQFN-48-1EP_7x7mm_P0.5mm_EP4.1x4.1mm,296-51057-1-ND
U20,1,SN74LVC2G06,,,,Package_TO_SOT_SMD:SOT-363_SC-70-6,296-13493-1-ND
U21,1,TPS53119,,,,Package_DFN_QFN:VQFN-16-1EP_3x3mm_P0.5mm_EP1.45x1.45mm,296-51985-1-ND
"U22,U23",2,TPS54308,,,,Package_TO_SOT_SMD:SOT-23-6,296-46237-1-ND
U24,1,CSD87352Q5D,,,,fmcw_:Texas_8-LSON_5x6mm,296-29161-1-ND
U25,1,SN74LVC1G06,,,,Package_TO_SOT_SMD:SOT-353_SC-70-5,296-8484-1-ND
U27,1,TPS3839G18DBZR,,,,Package_TO_SOT_SMD:SOT-23,296-40761-1-ND
U28,1,AP22816AKEWT,,,,Package_TO_SOT_SMD:SOT-23-5,31-AP22816AKEWT-7CT-ND
U29,1,USB3300-EZK,,,,Package_DFN_QFN:QFN-32-1EP_5x5mm_P0.5mm_EP3.45x3.45mm,638-1034-ND
U30,1,FT231XQ,,,,Package_DFN_QFN:QFN-20-1EP_4x4mm_P0.5mm_EP2.5x2.5mm,
U31,1,MCP3221,,,,Package_TO_SOT_SMD:SOT-23-5,MCP3221A5T-E/OTCT-ND
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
